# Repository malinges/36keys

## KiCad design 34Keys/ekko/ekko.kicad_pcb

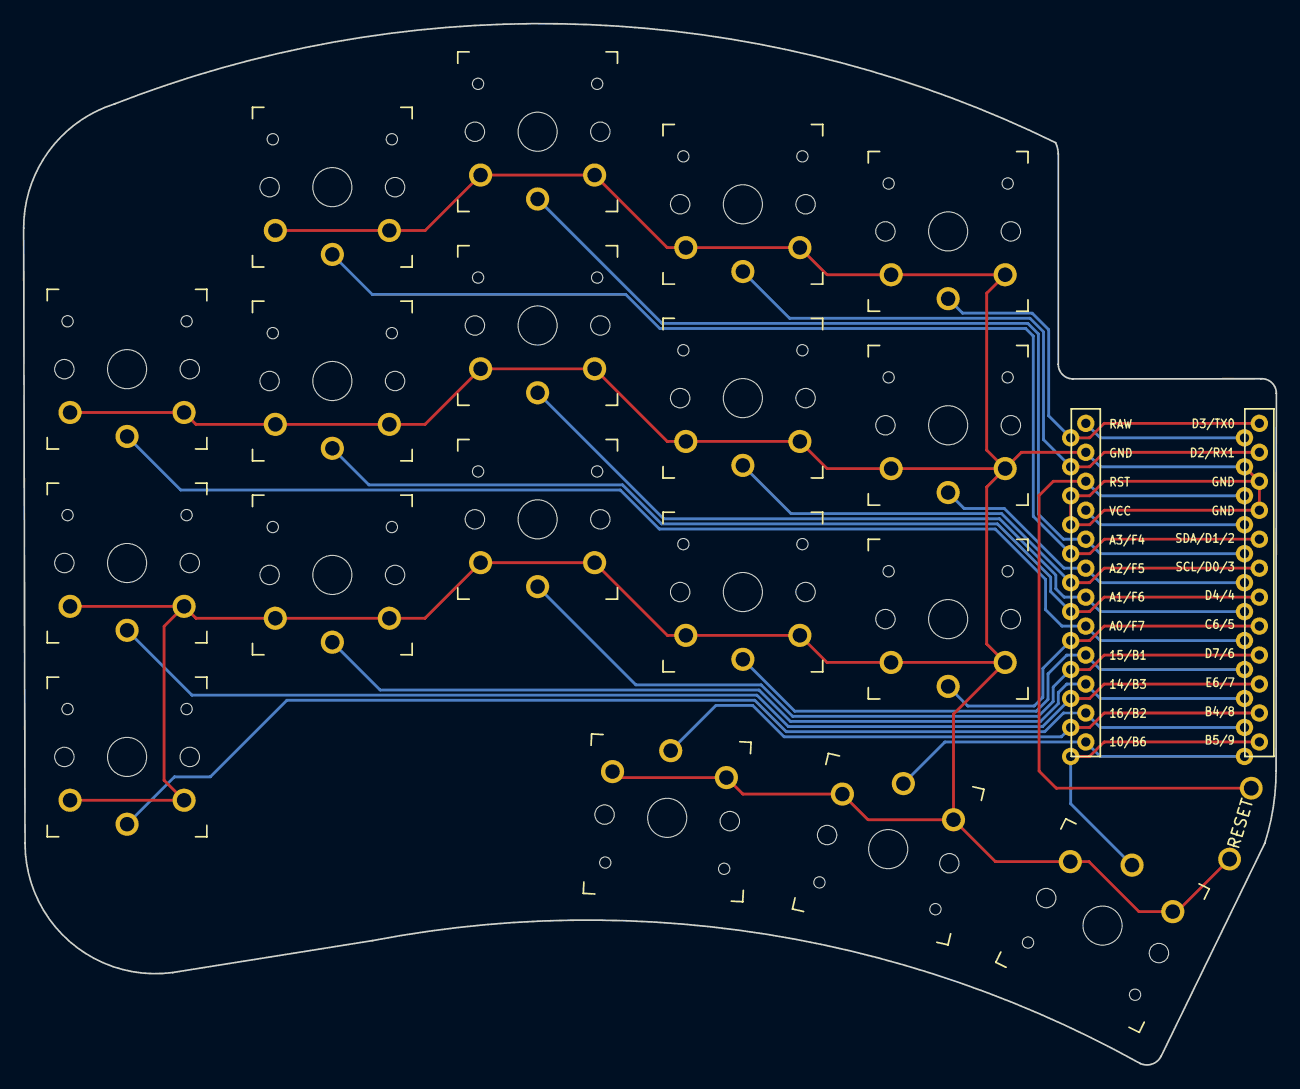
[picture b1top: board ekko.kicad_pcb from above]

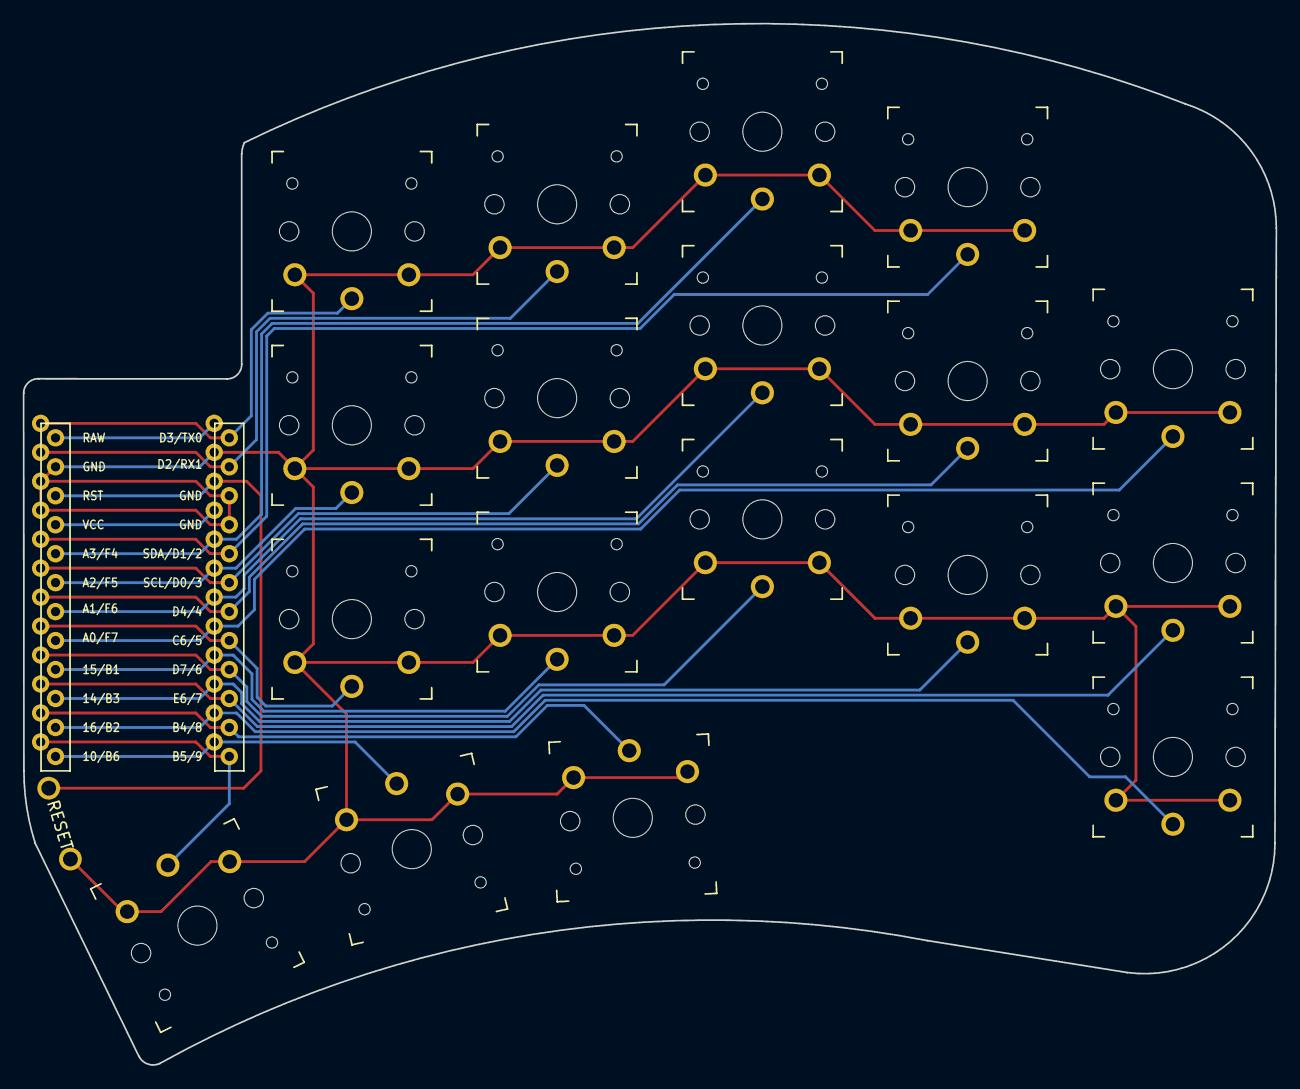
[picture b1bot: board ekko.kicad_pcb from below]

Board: 2 copper layers, 109.8 x 91.3 mm, 20 parts (3 on the bottom side), 22 nets.

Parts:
RSW1: Val**; ResetSW
SW2, SW3, SW4, SW5, SW6, SW8, SW9, SW10, SW11, SW12, SW14, SW15, SW16, SW17, SW18, SW20, SW20#2, SW21: SW_PUSH; SW_PG1350_reversible_b2
U1: ProMicro; ProMicro_v2

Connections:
GND: RSW1.1, SW2.2, SW3.2, SW4.2, SW5.2, SW6.2, SW8.2, SW9.2, SW10.2, SW11.2, SW12.2, SW14.2, SW15.2, SW16.2, SW17.2, SW18.2, SW20.2, SW20#2.2, SW21.2, U1.3, U1.4, U1.9, U1.10, U1.14, U1.23
LED: SW6.1, U1.1, U1.12
unnamed: SW4.1, U1.17, U1.20
unnamed: SW20.1, U1.2, U1.11
unnamed: SW21.1, U1.1, U1.12
unnamed: SW20#2.1, U1.13, U1.24
unnamed: SW14.1, U1.14, U1.23
unnamed: U1.13, U1.24
SCL: SW11.1, U1.6, U1.7
SDA: SW3.1, U1.5, U1.8
VCC: U1.16, U1.21
col1: SW12.1, U1.18, U1.19
col2: SW10.1, U1.18, U1.19
col3: SW2.1, U1.17, U1.20
col4: SW17.1, U1.16, U1.21
col5: SW15.1, U1.15, U1.22
data: SW5.1, U1.2, U1.11
reset: RSW1.2, U1.15, U1.22
row0: SW9.1, U1.6, U1.7
row1: SW18.1, U1.5, U1.8
row2: SW16.1, U1.4, U1.9
row3: SW8.1, U1.3, U1.10

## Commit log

2021-10-17 36-key version of the Ekko
2021-10-17 redo some tracks
